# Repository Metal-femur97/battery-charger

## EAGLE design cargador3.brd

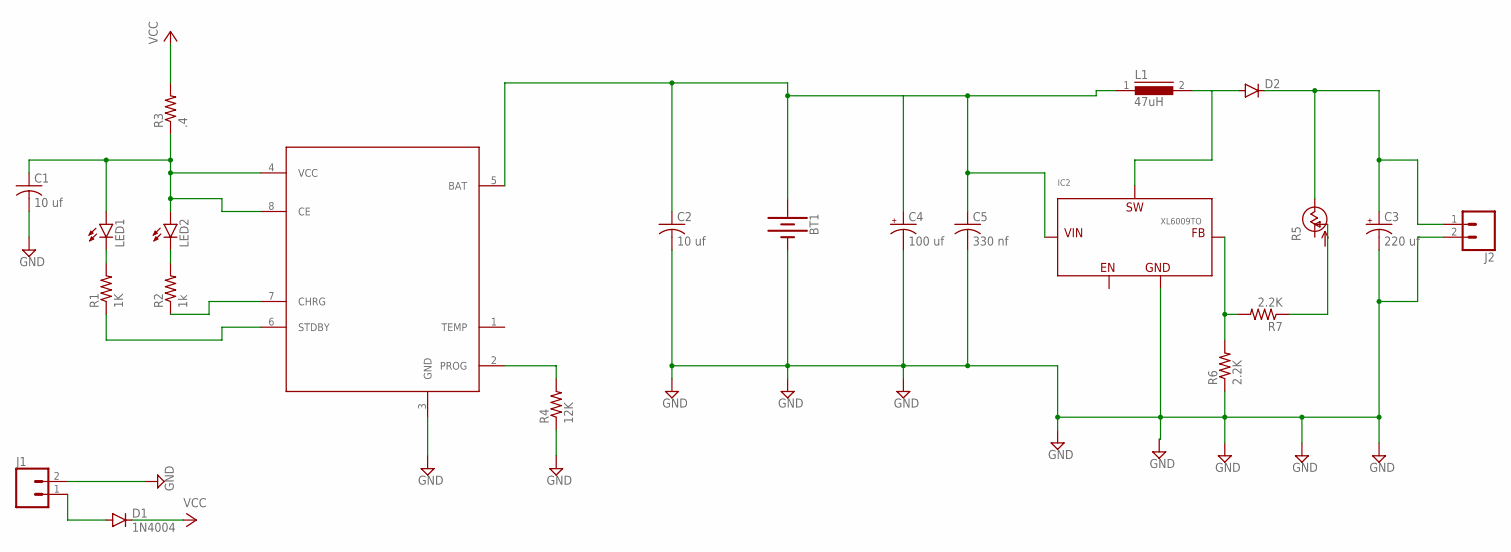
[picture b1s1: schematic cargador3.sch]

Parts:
BT1: BATTERY-18650; BATTERY_18650-HOLDER
C1, C2: 10 uf; C0402
C3: 220 uf; 140CLH-1010
C4: 100 uf; 140CLH-1010
C5: 330 nf; C0805
D1: 1N4004; DO41-10
D2: DIODE-DO214AA; DO214AA
IC2: XL6009TO; TO263-5L
J1, J2: CONN_02; 1X02
L1: 47uH; SRR1210
LED1, LED2: LEDSMART-LED; SMART-LED
R1: 1K; R1206
R2: 1k; R1206
R3: .4; R2010
R4: 12K; R0402
R5: POTTRB64Y; B64Y
R6, R7: 2.2K; R2010
TC4056: TC4056A

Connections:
GND: BT1.GND@1 (-), C1.2, C2.2, C3.-, C4.-, C5.2, IC2.1 (GND), J1.2, J2.2, R4.1, R6.1, TC4056.3 (GND)
unnamed: LED1.B (C), R1.2
unnamed: LED2.B (C), R2.2
unnamed: R4.2, TC4056.2 (PROG)
unnamed: R2.1, TC4056.7 (CHRG)
unnamed: R1.1, TC4056.6 (STDBY)
unnamed: C1.1, LED1.A, LED2.A, R3.1, TC4056.4 (VCC), TC4056.8 (CE)
unnamed: D2.A, IC2.3 (SW), L1.2
unnamed: D1.A, J1.1
unnamed: R5.S (OUT), R7.1
unnamed: C3.+, D2.C, J2.1, R5.E (VSS)
unnamed: BT1.PWR@1 (+), C2.1, C4.+, C5.1, IC2.4 (VIN), L1.1, TC4056.5 (BAT)
unnamed: IC2.5 (FB), R6.2, R7.2
VCC: D1.C, R3.2

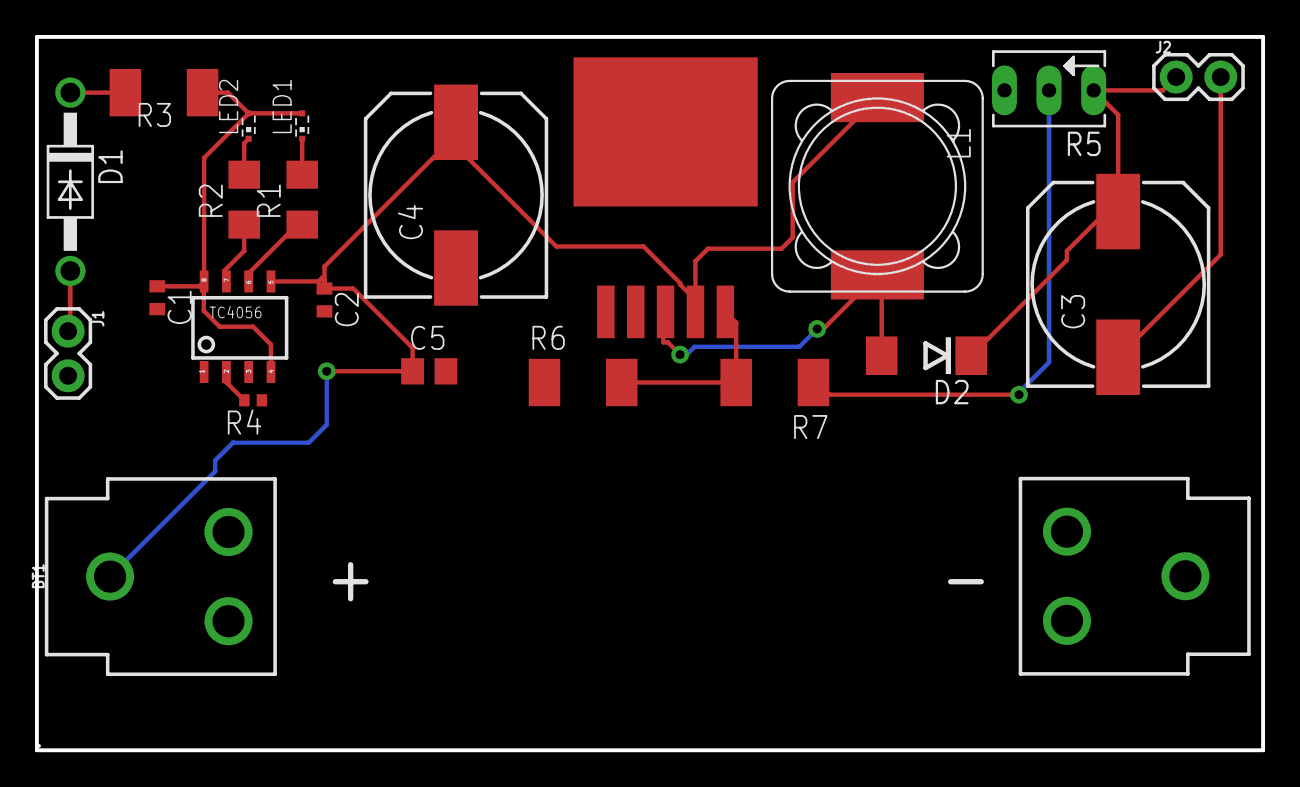
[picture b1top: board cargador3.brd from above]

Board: 2 copper layers, 69.8 x 40.6 mm, 22 parts (0 on the bottom side), 14 nets.

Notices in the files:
parts and their libraries:
SparkFun-Connectors: Licensing: Creative Commons ShareAlike 4.0 International - https://creativecommons.org/licenses/by-sa/4.0
